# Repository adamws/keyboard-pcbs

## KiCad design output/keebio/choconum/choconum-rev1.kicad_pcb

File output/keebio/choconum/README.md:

## keebio/choconum/choconum-rev1

[layout](choconum-rev1-kle.json) - [PCB](choconum-rev1.kicad_pcb)

{:loading="lazy"}

[Open in keyboard-layout-editor](http://www.keyboard-layout-editor.com/##@@=0,0&=0,1&=0,2&=0,3;&@=1,0&=1,1&=1,2&_h:2;&=1,3%0A%0A%0A1,0;&@=2,0&=2,1&=2,2;&@=3,0&=3,1&=3,2&_h:2;&=3,3%0A%0A%0A2,0;&@_w:2;&=4,0%0A%0A%0A0,0&=4,2;&@_x:4.5&y:-4;&=1,3%0A%0A%0A1,1;&@_x:4.5;&=2,3%0A%0A%0A1,1;&@_x:4.5;&=3,3%0A%0A%0A2,1;&@_x:4.5;&=4,3%0A%0A%0A2,1;&@_y:0.5;&=4,0%0A%0A%0A0,1&=4,1%0A%0A%0A0,1)

{:loading="lazy"}

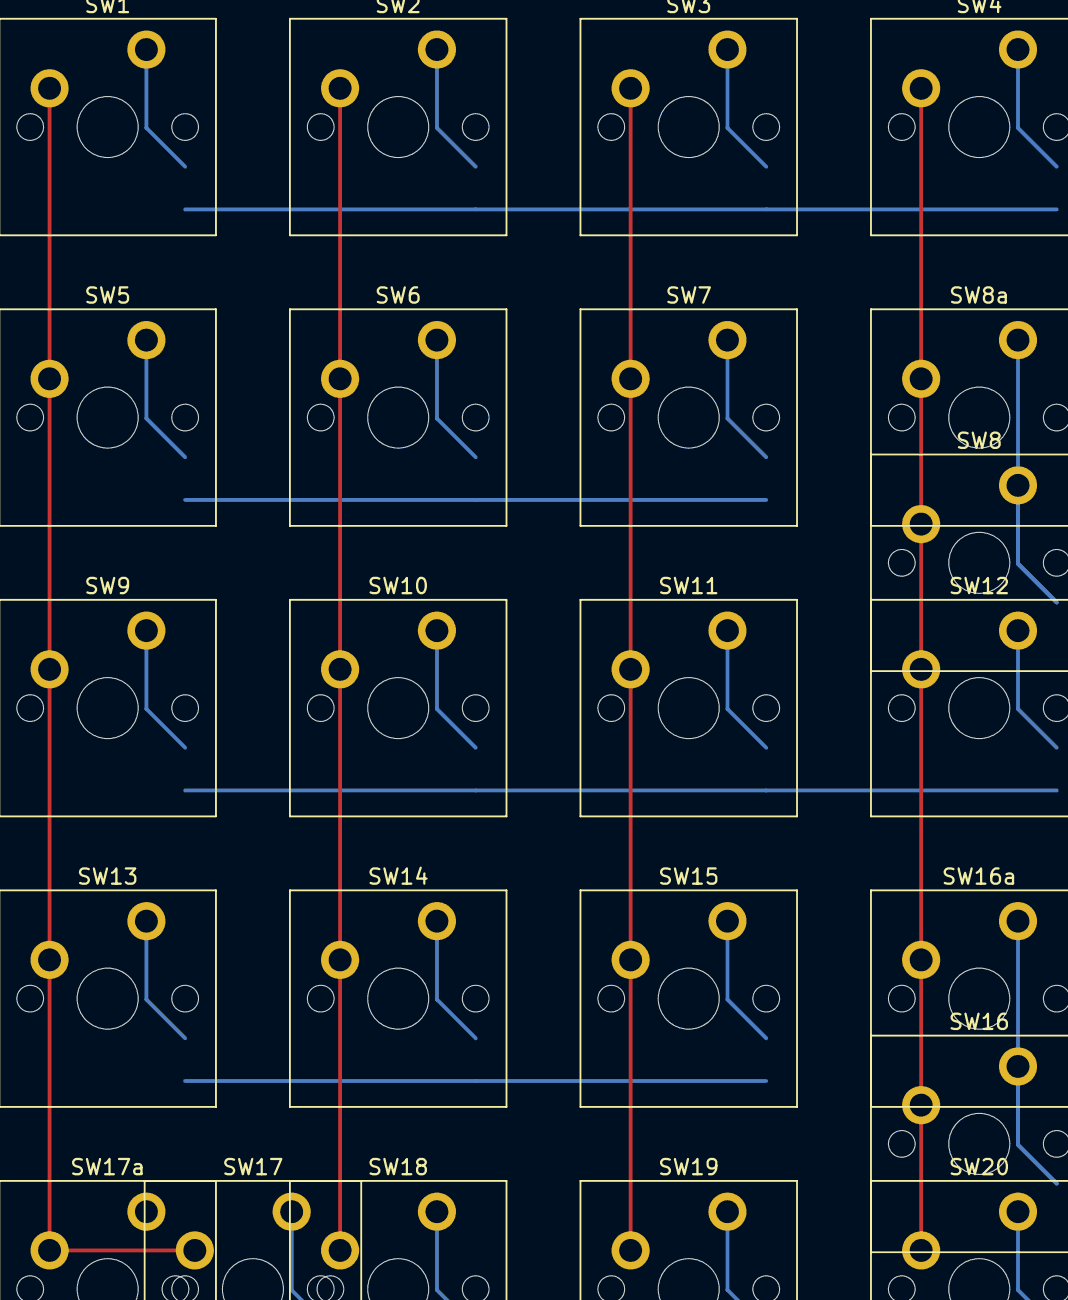
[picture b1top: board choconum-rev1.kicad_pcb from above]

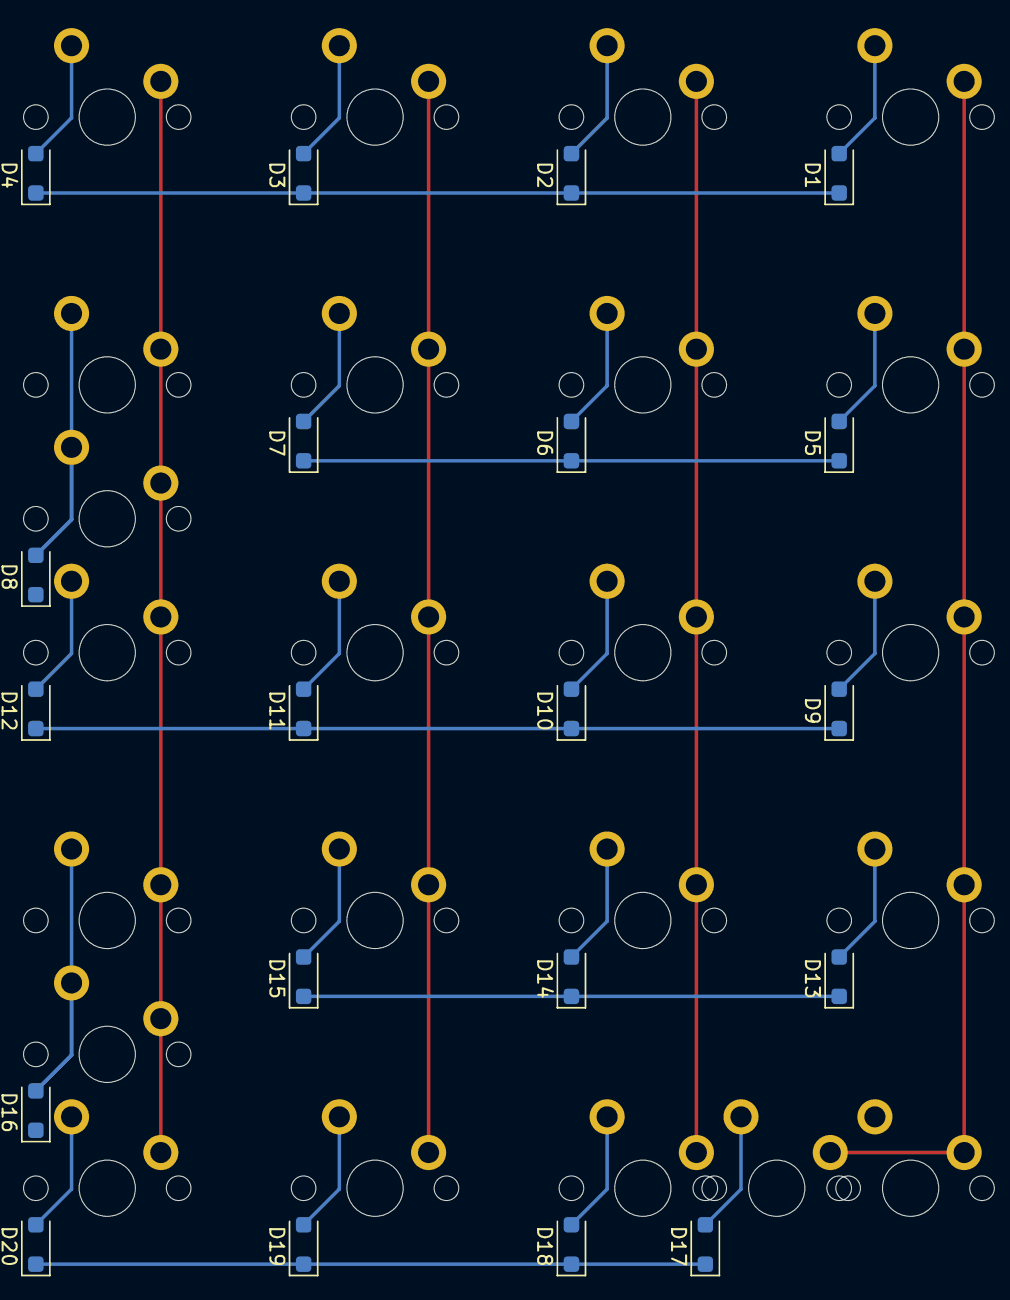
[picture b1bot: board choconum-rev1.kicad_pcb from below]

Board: 2 copper layers, 43 parts (20 on the bottom side), 29 nets.

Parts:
D1, D2, D3, D4, D5, D6, D7, D8, D9, D10, D11, D12, D13, D14, D15, D16, D17, D18, D19, D20: D_SOD-123F
SW1, SW2, SW3, SW4, SW5, SW6, SW7, SW8, SW8a, SW9, SW10, SW11, SW12, SW13, SW14, SW15, SW16, SW16a, SW17, SW17a, SW18, SW19, SW20: SW_Cherry_MX_PCB_1.00u

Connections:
COL0: SW1.1, SW5.1, SW9.1, SW13.1, SW17.1, SW17a.1
COL1: SW2.1, SW6.1, SW10.1, SW14.1, SW18.1
COL2: SW3.1, SW7.1, SW11.1, SW15.1, SW19.1
COL3: SW4.1, SW8.1, SW8a.1, SW12.1, SW16.1, SW16a.1, SW20.1
unnamed: D1.2, SW1.2
unnamed: D2.2, SW2.2
unnamed: D3.2, SW3.2
unnamed: D4.2, SW4.2
unnamed: D5.2, SW5.2
unnamed: D6.2, SW6.2
unnamed: D7.2, SW7.2
unnamed: D8.2, SW8.2, SW8a.2
unnamed: D9.2, SW9.2
unnamed: D10.2, SW10.2
unnamed: D11.2, SW11.2
unnamed: D12.2, SW12.2
unnamed: D13.2, SW13.2
unnamed: D14.2, SW14.2
unnamed: D15.2, SW15.2
unnamed: D16.2, SW16.2, SW16a.2
unnamed: D17.2, SW17.2, SW17a.2
unnamed: D18.2, SW18.2
unnamed: D19.2, SW19.2
unnamed: D20.2, SW20.2
ROW0: D1.1, D2.1, D3.1, D4.1
ROW1: D5.1, D6.1, D7.1, D8.1
ROW2: D9.1, D10.1, D11.1, D12.1
ROW3: D13.1, D14.1, D15.1, D16.1
ROW4: D17.1, D18.1, D19.1, D20.1

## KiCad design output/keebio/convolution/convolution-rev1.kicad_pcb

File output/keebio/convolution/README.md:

## keebio/convolution/convolution-rev1

[layout](convolution-rev1-kle.json) - [PCB](convolution-rev1.kicad_pcb)

{:loading="lazy"}

[Open in keyboard-layout-editor](http://www.keyboard-layout-editor.com/##@@_x:3.0&c=#aaaaaa;&=0,0%0A%0A%0A0,0&=0,1&_x:0.25&c=#777777;&=0,2&_c=#cccccc;&=0,3&=0,4&=0,5&=0,6&=0,7&=0,8&=0,9&=0,10&=0,11&=0,12&=0,13&=0,14&_c=#aaaaaa&w:2;&=0,15%0A%0A%0A2,0&=0,17%0A%0A%0A1,0;&@_x:3;&=1,0&=1,1&_x:0.25&w:1.5;&=1,2&_c=#cccccc;&=1,3&=1,4&=1,5&=1,6&=1,7&=1,8&=1,9&=1,10&=1,11&=1,12&=1,13&=1,14&_c=#aaaaaa&w:1.5;&=1,15%0A%0A%0A6,0&=1,17;&@_x:3;&=2,0&=2,1&_x:0.25&w:1.75;&=2,2&_c=#cccccc;&=2,3&=2,4&=2,5&=2,6&=2,7&=2,8&=2,9&=2,10&=2,11&=2,12&=2,13&_c=#777777&w:2.25;&=2,15%0A%0A%0A6,0&_c=#aaaaaa;&=2,17;&@_x:3.0;&=3,0&=3,1&_x:0.25&w:2.25;&=3,2%0A%0A%0A4,0&_c=#cccccc;&=3,4&=3,5&=3,6&=3,7&=3,8&=3,9&=3,10&=3,11&=3,12&=3,13&_c=#aaaaaa&w:1.75;&=3,14%0A%0A%0A5,0&=3,15%0A%0A%0A5,0&=3,17;&@_x:3;&=4,0&=4,1&_x:0.25&w:1.25;&=4,2&_w:1.25;&=4,3&_w:1.25;&=4,4&_c=#cccccc&w:6.25;&=4,8%0A%0A%0A3,0&_c=#aaaaaa;&=4,11&=4,12&=4,13&=4,14&=4,15&=4,17;&@_x:1.25&y:-5;&=0,0%0A%0A%0A0,1%0A%0A%0A%0A%0A%0Ae0&_x:20.0;&=0,15%0A%0A%0A2,1&=0,16%0A%0A%0A2,1&=0,17%0A%0A%0A1,1%0A%0A%0A%0A%0A%0Ae1;&@_x:23.0&c=#777777&w:1.25&h:2&w2:1.5&h2:1&x2:-0.25;&=2,15%0A%0A%0A6,1;&@_x:22.0&c=#aaaaaa;&=2,14%0A%0A%0A6,1;&@_w:1.25;&=3,2%0A%0A%0A4,1&=3,3%0A%0A%0A4,1&_x:19.25&w:2.75;&=3,14%0A%0A%0A5,1;&@_x:9&y:1&c=#cccccc&w:1.25;&=4,5%0A%0A%0A3,1&_w:2.25;&=4,8%0A%0A%0A3,1&_w:2.75;&=4,9%0A%0A%0A3,1;&@_x:9&w:2.25;&=4,5%0A%0A%0A3,2&_w:1.25;&=4,8%0A%0A%0A3,2&_w:2.75;&=4,9%0A%0A%0A3,2)

{:loading="lazy"}

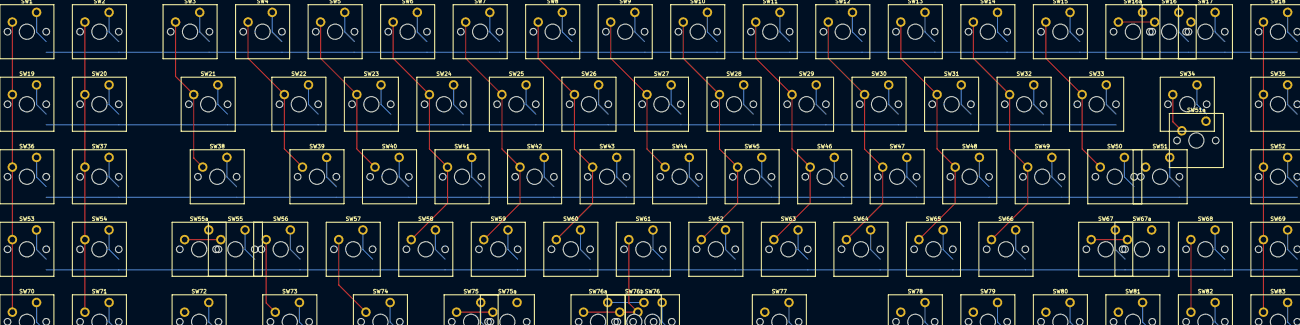
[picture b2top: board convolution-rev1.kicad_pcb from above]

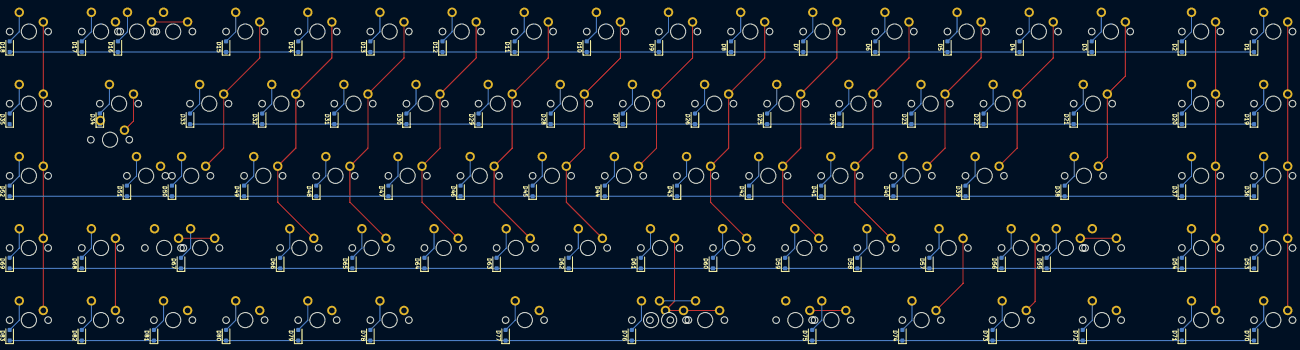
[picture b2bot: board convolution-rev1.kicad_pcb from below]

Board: 2 copper layers, 173 parts (83 on the bottom side), 105 nets.

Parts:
D1, D2, D3, D4, D5, D6, D7, D8, D9, D10, D11, D12, D13, D14, D15, D16, D17, D18, D19, D20, D21, D22, D23, D24, D25, D26, D27, D28, D29, D30, D31, D32, D33, D34, D35, D36, D37, D38, D39, D40, D41, D42, D43, D44, D45, D46, D47, D48, D49, D50, D51, D52, D53, D54, D55, D56, D57, D58, D59, D60, D61, D62, D63, D64, D65, D66, D67, D68, D69, D70, D71, D72, D73, D74, D75, D76, D77, D78, D79, D80, D81, D82, D83: D_SOD-123F
SW1, SW2, SW3, SW4, SW5, SW6, SW7, SW8, SW9, SW10, SW11, SW12, SW13, SW14, SW15, SW16, SW16a, SW17, SW18, SW19, SW20, SW21, SW22, SW23, SW24, SW25, SW26, SW27, SW28, SW29, SW30, SW31, SW32, SW33, SW34, SW35, SW36, SW37, SW38, SW39, SW40, SW41, SW42, SW43, SW44, SW45, SW46, SW47, SW48, SW49, SW50, SW51, SW51a, SW52, SW53, SW54, SW55, SW55a, SW56, SW57, SW58, SW59, SW60, SW61, SW62, SW63, SW64, SW65, SW66, SW67, SW67a, SW68, SW69, SW70, SW71, SW72, SW73, SW74, SW75, SW75a, SW76, SW76a, SW76b, SW77, SW78, SW79, SW80, SW81, SW82, SW83: SW_Cherry_MX_PCB_1.00u

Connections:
COL0: SW1.1, SW19.1, SW36.1, SW53.1, SW70.1
COL1: SW2.1, SW20.1, SW37.1, SW54.1, SW71.1
COL2: SW3.1, SW21.1, SW38.1, SW55.1, SW55a.1, SW72.1
COL3: SW4.1, SW22.1, SW39.1, SW56.1, SW73.1
COL4: SW5.1, SW23.1, SW40.1, SW57.1, SW74.1
COL5: SW6.1, SW24.1, SW41.1, SW58.1, SW75.1, SW75a.1
COL6: SW7.1, SW25.1, SW42.1, SW59.1
COL7: SW8.1, SW26.1, SW43.1, SW60.1
COL8: SW9.1, SW27.1, SW44.1, SW61.1, SW76.1, SW76a.1, SW76b.1
COL9: SW10.1, SW28.1, SW45.1, SW62.1, SW77.1
COL10: SW11.1, SW29.1, SW46.1, SW63.1
COL11: SW12.1, SW30.1, SW47.1, SW64.1, SW78.1
COL12: SW13.1, SW31.1, SW48.1, SW65.1, SW79.1
COL13: SW14.1, SW32.1, SW49.1, SW66.1, SW80.1
COL14: SW15.1, SW33.1, SW50.1, SW67.1, SW67a.1, SW81.1
COL15: SW16.1, SW16a.1, SW34.1, SW51.1, SW51a.1, SW68.1, SW82.1
COL17: SW18.1, SW35.1, SW52.1, SW69.1, SW83.1
unnamed: D1.2, SW1.2
unnamed: D2.2, SW2.2
unnamed: D3.2, SW3.2
unnamed: D4.2, SW4.2
unnamed: D5.2, SW5.2
unnamed: D6.2, SW6.2
unnamed: D7.2, SW7.2
unnamed: D8.2, SW8.2
unnamed: D9.2, SW9.2
unnamed: D10.2, SW10.2
unnamed: D11.2, SW11.2
unnamed: D12.2, SW12.2
unnamed: D13.2, SW13.2
unnamed: D14.2, SW14.2
unnamed: D15.2, SW15.2
unnamed: D16.2, SW16.2, SW16a.2
unnamed: D17.2, SW17.2
unnamed: D18.2, SW18.2
unnamed: D19.2, SW19.2
unnamed: D20.2, SW20.2
unnamed: D21.2, SW21.2
unnamed: D22.2, SW22.2
unnamed: D23.2, SW23.2
unnamed: D24.2, SW24.2
unnamed: D25.2, SW25.2
unnamed: D26.2, SW26.2
unnamed: D27.2, SW27.2
unnamed: D28.2, SW28.2
unnamed: D29.2, SW29.2
unnamed: D30.2, SW30.2
unnamed: D31.2, SW31.2
unnamed: D32.2, SW32.2
unnamed: D33.2, SW33.2
unnamed: D34.2, SW34.2
unnamed: D35.2, SW35.2
unnamed: D36.2, SW36.2
unnamed: D37.2, SW37.2
unnamed: D38.2, SW38.2
unnamed: D39.2, SW39.2
unnamed: D40.2, SW40.2
unnamed: D41.2, SW41.2
unnamed: D42.2, SW42.2
unnamed: D43.2, SW43.2
unnamed: D44.2, SW44.2
unnamed: D45.2, SW45.2
unnamed: D46.2, SW46.2
unnamed: D47.2, SW47.2
unnamed: D48.2, SW48.2
unnamed: D49.2, SW49.2
unnamed: D50.2, SW50.2
unnamed: D51.2, SW51.2, SW51a.2
unnamed: D52.2, SW52.2
unnamed: D53.2, SW53.2
unnamed: D54.2, SW54.2
unnamed: D55.2, SW55.2, SW55a.2
unnamed: D56.2, SW56.2
unnamed: D57.2, SW57.2
unnamed: D58.2, SW58.2
unnamed: D59.2, SW59.2
unnamed: D60.2, SW60.2
unnamed: D61.2, SW61.2
unnamed: D62.2, SW62.2
unnamed: D63.2, SW63.2
unnamed: D64.2, SW64.2
unnamed: D65.2, SW65.2
unnamed: D66.2, SW66.2
unnamed: D67.2, SW67.2, SW67a.2
unnamed: D68.2, SW68.2
unnamed: D69.2, SW69.2
unnamed: D70.2, SW70.2
unnamed: D71.2, SW71.2
unnamed: D72.2, SW72.2
unnamed: D73.2, SW73.2
unnamed: D74.2, SW74.2
unnamed: D75.2, SW75.2, SW75a.2
unnamed: D76.2, SW76.2, SW76a.2, SW76b.2
unnamed: D77.2, SW77.2
unnamed: D78.2, SW78.2
unnamed: D79.2, SW79.2
unnamed: D80.2, SW80.2
unnamed: D81.2, SW81.2
unnamed: D82.2, SW82.2
unnamed: D83.2, SW83.2
ROW0: D1.1, D2.1, D3.1, D4.1, D5.1, D6.1, D7.1, D8.1, D9.1, D10.1, D11.1, D12.1, D13.1, D14.1, D15.1, D16.1, D17.1, D18.1
ROW1: D19.1, D20.1, D21.1, D22.1, D23.1, D24.1, D25.1, D26.1, D27.1, D28.1, D29.1, D30.1, D31.1, D32.1, D33.1, D34.1, D35.1
ROW2: D36.1, D37.1, D38.1, D39.1, D40.1, D41.1, D42.1, D43.1, D44.1, D45.1, D46.1, D47.1, D48.1, D49.1, D50.1, D51.1, D52.1
ROW3: D53.1, D54.1, D55.1, D56.1, D57.1, D58.1, D59.1, D60.1, D61.1, D62.1, D63.1, D64.1, D65.1, D66.1, D67.1, D68.1, D69.1
ROW4: D70.1, D71.1, D72.1, D73.1, D74.1, D75.1, D76.1, D77.1, D78.1, D79.1, D80.1, D81.1, D82.1, D83.1

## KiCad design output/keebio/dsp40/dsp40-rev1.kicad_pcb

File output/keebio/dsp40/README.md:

## keebio/dsp40/dsp40-rev1

[layout](dsp40-rev1-kle.json) - [PCB](dsp40-rev1.kicad_pcb)

{:loading="lazy"}

[Open in keyboard-layout-editor](http://www.keyboard-layout-editor.com/##@@_c=#777777;&=0,0&_c=#cccccc;&=0,1&=0,2&=0,3&=0,4&=0,5&=0,6&=0,7&=0,8&=0,9&=0,10&_c=#aaaaaa;&=0,11;&@_w:1.25;&=1,0%0A%0A%0A0,0&_c=#cccccc;&=1,1%0A%0A%0A0,0&=1,2%0A%0A%0A0,0&=1,3%0A%0A%0A0,0&=1,4%0A%0A%0A0,0&=1,5%0A%0A%0A0,0&=1,6%0A%0A%0A0,0&=1,7%0A%0A%0A0,0&=1,8%0A%0A%0A0,0&=1,9%0A%0A%0A0,0&_c=#777777&w:1.75;&=1,11%0A%0A%0A0,0;&@_c=#aaaaaa&w:1.75;&=2,1%0A%0A%0A1,0&_c=#cccccc;&=2,2%0A%0A%0A1,0&=2,3%0A%0A%0A1,0&=2,4%0A%0A%0A1,0&=2,5%0A%0A%0A1,0&=2,6%0A%0A%0A1,0&=2,7%0A%0A%0A1,0&=2,8%0A.%0A%0A1,0&=2,9%0A%0A%0A1,0&_w:1.25;&=2,10%0A%0A%0A1,0&_c=#aaaaaa;&=2,11%0A%0A%0A1,0;&@_w:1.25;&=3,0%0A%0A%0A2,0&=3,1%0A%0A%0A2,0&_w:1.25;&=3,2%0A%0A%0A2,0&_c=#cccccc&w:2.25;&=3,4%0A%0A%0A2,0&_w:2.75;&=3,7%0A%0A%0A2,0&_c=#aaaaaa&w:1.25;&=3,9%0A%0A%0A2,0&=3,10%0A%0A%0A2,0&_w:1.25;&=3,11%0A%0A%0A2,0;&@_x:12.5&y:-3;&=1,0%0A%0A%0A0,1&_c=#cccccc;&=1,1%0A%0A%0A0,1&=1,2%0A%0A%0A0,1&=1,3%0A%0A%0A0,1&=1,4%0A%0A%0A0,1&=1,5%0A%0A%0A0,1&=1,6%0A%0A%0A0,1&=1,7%0A%0A%0A0,1&=1,8%0A%0A%0A0,1&=1,9%0A%0A%0A0,1&=1,10%0A%0A%0A0,1&_c=#aaaaaa;&=1,11%0A%0A%0A0,1;&@_x:12.5&w:1.75;&=2,1%0A%0A%0A1,1&_c=#cccccc;&=2,2%0A%0A%0A1,1&=2,3%0A%0A%0A1,1&=2,4%0A%0A%0A1,1&=2,5%0A%0A%0A1,1&=2,6%0A%0A%0A1,1&=2,7%0A%0A%0A1,1&=2,8%0A.%0A%0A1,1&=2,9%0A%0A%0A1,1&=2,10%0A%0A%0A1,1&_c=#aaaaaa&w:1.25;&=2,11%0A%0A%0A1,1;&@_x:12.5;&=2,0%0A%0A%0A1,2&_c=#cccccc;&=2,1%0A%0A%0A1,2&=2,2%0A%0A%0A1,2&=2,3%0A%0A%0A1,2&=2,4%0A%0A%0A1,2&=2,5%0A%0A%0A1,2&=2,6%0A%0A%0A1,2&=2,7%0A%0A%0A1,2&=2,8%0A%0A%0A1,2&=2,9%0A%0A%0A1,2&=2,10%0A%0A%0A1,2&_c=#777777;&=2,11%0A%0A%0A1,2;&@_y:0.25&c=#aaaaaa&w:1.5;&=3,0%0A%0A%0A2,1&=3,1%0A%0A%0A2,1&_w:1.5;&=3,2%0A%0A%0A2,1&_c=#cccccc&w:2.25;&=3,4%0A%0A%0A2,1&_w:2.75;&=3,7%0A%0A%0A2,1&_c=#aaaaaa;&=3,9%0A%0A%0A2,1&=3,10%0A%0A%0A2,1&=3,11%0A%0A%0A2,1;&@_y:0.25;&=3,0%0A%0A%0A2,2&=3,1%0A%0A%0A2,2&=3,2%0A%0A%0A2,2&=3,3%0A%0A%0A2,2&=3,4%0A%0A%0A2,2&_c=#cccccc;&=3,5%0A%0A%0A2,2&=3,6%0A%0A%0A2,2&_c=#aaaaaa;&=3,7%0A%0A%0A2,2&=3,8%0A%0A%0A2,2&=3,9%0A%0A%0A2,2&=3,10%0A%0A%0A2,2&=3,11%0A%0A%0A2,2)

{:loading="lazy"}

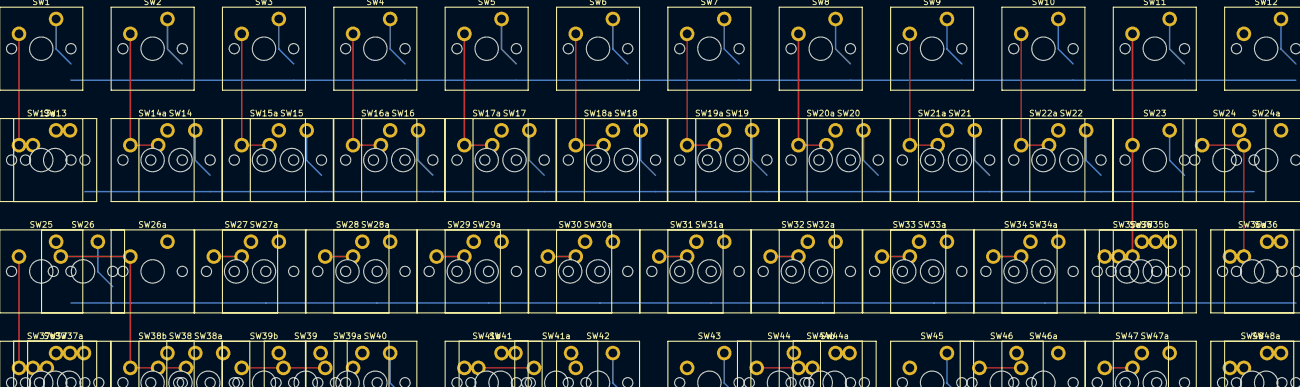
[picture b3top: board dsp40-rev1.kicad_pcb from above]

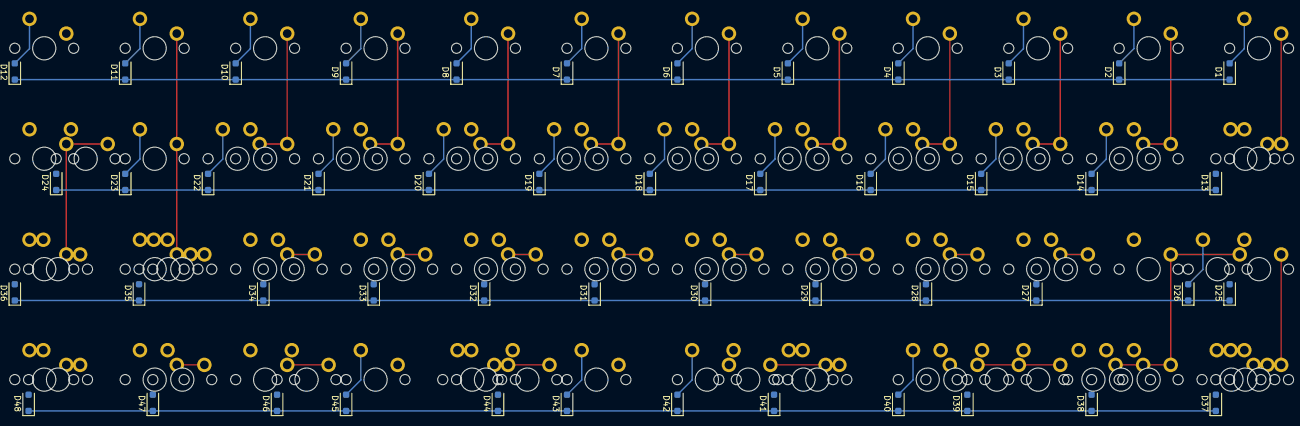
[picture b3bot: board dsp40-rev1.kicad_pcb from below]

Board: 2 copper layers, 132 parts (48 on the bottom side), 64 nets.

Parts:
D1, D2, D3, D4, D5, D6, D7, D8, D9, D10, D11, D12, D13, D14, D15, D16, D17, D18, D19, D20, D21, D22, D23, D24, D25, D26, D27, D28, D29, D30, D31, D32, D33, D34, D35, D36, D37, D38, D39, D40, D41, D42, D43, D44, D45, D46, D47, D48: D_SOD-123F
SW1, SW2, SW3, SW4, SW5, SW6, SW7, SW8, SW9, SW10, SW11, SW12, SW13, SW13a, SW14, SW14a, SW15, SW15a, SW16, SW16a, SW17, SW17a, SW18, SW18a, SW19, SW19a, SW20, SW20a, SW21, SW21a, SW22, SW22a, SW23, SW24, SW24a, SW25, SW26, SW26a, SW27, SW27a, SW28, SW28a, SW29, SW29a, SW30, SW30a, SW31, SW31a, SW32, SW32a, SW33, SW33a, SW34, SW34a, SW35, SW35a, SW35b, SW36, SW36a, SW37, SW37a, SW37b, SW38, SW38a, SW38b, SW39, SW39a, SW39b, SW40, SW41, SW41a, SW41b, SW42, SW43, SW44, SW44a, SW44b, SW45, SW46, SW46a, SW47, SW47a, SW48, SW48a: SW_Cherry_MX_PCB_1.00u

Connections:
COL0: SW1.1, SW13.1, SW13a.1, SW25.1, SW37.1, SW37a.1, SW37b.1
COL1: SW2.1, SW14.1, SW14a.1, SW26.1, SW26a.1, SW38.1, SW38a.1, SW38b.1
COL2: SW3.1, SW15.1, SW15a.1, SW27.1, SW27a.1, SW39.1, SW39a.1, SW39b.1
COL3: SW4.1, SW16.1, SW16a.1, SW28.1, SW28a.1, SW40.1
COL4: SW5.1, SW17.1, SW17a.1, SW29.1, SW29a.1, SW41.1, SW41a.1, SW41b.1
COL5: SW6.1, SW18.1, SW18a.1, SW30.1, SW30a.1, SW42.1
COL6: SW7.1, SW19.1, SW19a.1, SW31.1, SW31a.1, SW43.1
COL7: SW8.1, SW20.1, SW20a.1, SW32.1, SW32a.1, SW44.1, SW44a.1, SW44b.1
COL8: SW9.1, SW21.1, SW21a.1, SW33.1, SW33a.1, SW45.1
COL9: SW10.1, SW22.1, SW22a.1, SW34.1, SW34a.1, SW46.1, SW46a.1
COL10: SW11.1, SW23.1, SW35.1, SW35a.1, SW35b.1, SW47.1, SW47a.1
COL11: SW12.1, SW24.1, SW24a.1, SW36.1, SW36a.1, SW48.1, SW48a.1
unnamed: D1.2, SW1.2
unnamed: D2.2, SW2.2
unnamed: D3.2, SW3.2
unnamed: D4.2, SW4.2
unnamed: D5.2, SW5.2
unnamed: D6.2, SW6.2
unnamed: D7.2, SW7.2
unnamed: D8.2, SW8.2
unnamed: D9.2, SW9.2
unnamed: D10.2, SW10.2
unnamed: D11.2, SW11.2
unnamed: D12.2, SW12.2
unnamed: D13.2, SW13.2, SW13a.2
unnamed: D14.2, SW14.2, SW14a.2
unnamed: D15.2, SW15.2, SW15a.2
unnamed: D16.2, SW16.2, SW16a.2
unnamed: D17.2, SW17.2, SW17a.2
unnamed: D18.2, SW18.2, SW18a.2
unnamed: D19.2, SW19.2, SW19a.2
unnamed: D20.2, SW20.2, SW20a.2
unnamed: D21.2, SW21.2, SW21a.2
unnamed: D22.2, SW22.2, SW22a.2
unnamed: D23.2, SW23.2
unnamed: D24.2, SW24.2, SW24a.2
unnamed: D25.2, SW25.2
unnamed: D26.2, SW26.2, SW26a.2
unnamed: D27.2, SW27.2, SW27a.2
unnamed: D28.2, SW28.2, SW28a.2
unnamed: D29.2, SW29.2, SW29a.2
unnamed: D30.2, SW30.2, SW30a.2
unnamed: D31.2, SW31.2, SW31a.2
unnamed: D32.2, SW32.2, SW32a.2
unnamed: D33.2, SW33.2, SW33a.2
unnamed: D34.2, SW34.2, SW34a.2
unnamed: D35.2, SW35.2, SW35a.2, SW35b.2
unnamed: D36.2, SW36.2, SW36a.2
unnamed: D37.2, SW37.2, SW37a.2, SW37b.2
unnamed: D38.2, SW38.2, SW38a.2, SW38b.2
unnamed: D39.2, SW39.2, SW39a.2, SW39b.2
unnamed: D40.2, SW40.2
unnamed: D41.2, SW41.2, SW41a.2, SW41b.2
unnamed: D42.2, SW42.2
unnamed: D43.2, SW43.2
unnamed: D44.2, SW44.2, SW44a.2, SW44b.2
unnamed: D45.2, SW45.2
unnamed: D46.2, SW46.2, SW46a.2
unnamed: D47.2, SW47.2, SW47a.2
unnamed: D48.2, SW48.2, SW48a.2
ROW0: D1.1, D2.1, D3.1, D4.1, D5.1, D6.1, D7.1, D8.1, D9.1, D10.1, D11.1, D12.1
ROW1: D13.1, D14.1, D15.1, D16.1, D17.1, D18.1, D19.1, D20.1, D21.1, D22.1, D23.1, D24.1
ROW2: D25.1, D26.1, D27.1, D28.1, D29.1, D30.1, D31.1, D32.1, D33.1, D34.1, D35.1, D36.1
ROW3: D37.1, D38.1, D39.1, D40.1, D41.1, D42.1, D43.1, D44.1, D45.1, D46.1, D47.1, D48.1
